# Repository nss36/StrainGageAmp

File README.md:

# StrainGageAmp
Nicholas Szczecinski 2020
West Virginia University
Morgantown, West Virginia, USA

EAGLE files for a 5V, 3-channel amplifier for 350 Ohm strain gages.

On Digikey:
Strain gauges -                    1033-1009-ND
3 LM324 Quad Op Amps -             296-1391-5-ND
9 352 Ohm 0603 SMD Resistors -     13-RT0603DRE07352RLCT-ND 
6 2.2 kOhm 0603 SMD Resistors -    P121436CT-ND
6 560 kOhm 0603 SMD Resistors -    749-1753-1-ND 

You will also need 11 pinheaders: one group of 5, and three groups of 2.

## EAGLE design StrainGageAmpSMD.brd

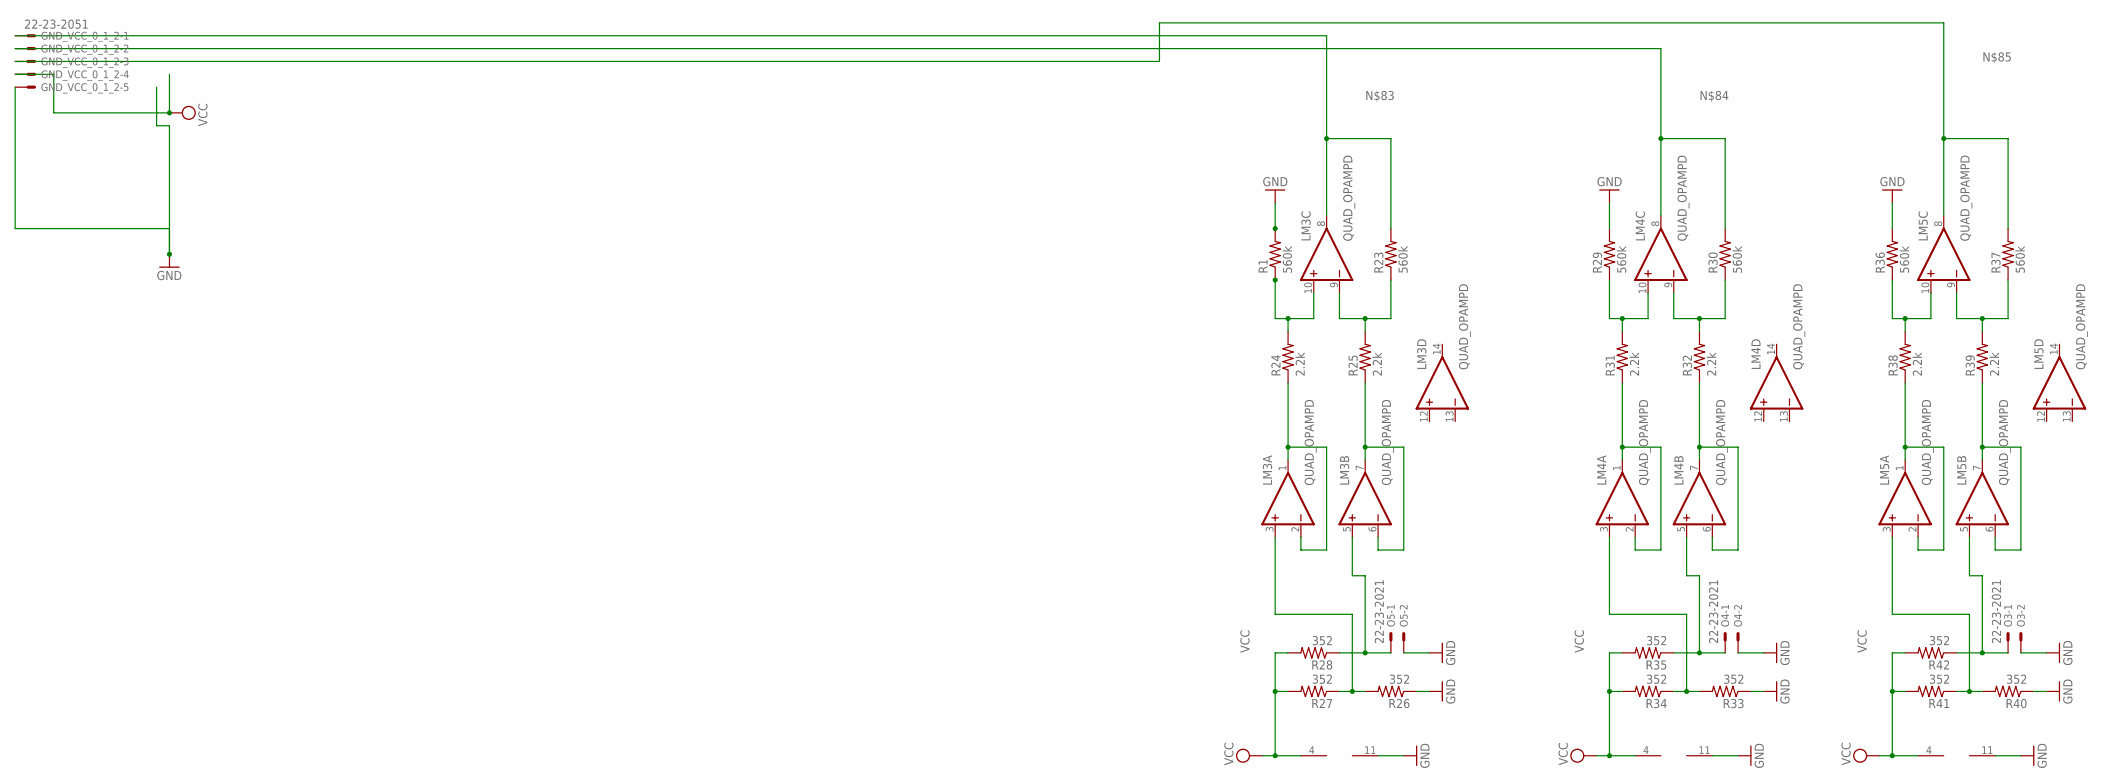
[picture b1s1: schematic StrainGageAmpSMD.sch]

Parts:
GND_VCC_0_1_2: 22-23-2051
LM3, LM4, LM5: QUAD_OPAMPD; SO14
O3, O4, O5: 22-23-2021
R1, R23, R29, R30, R36, R37: 560k; R0603
R24, R25, R31, R32, R38, R39: 2.2k; R0603
R26, R27, R28, R33, R34, R35, R40, R41, R42: 352; R0603

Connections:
GND: GND_VCC_0_1_2.5, LM3.11 (V-), LM4.11 (V-), LM5.11 (V-), O3.2, O4.2, O5.2, R1.2, R26.1, R29.2, R33.1, R36.2, R40.1
unnamed: LM3.3 (+IN), R26.2, R27.1
unnamed: LM3.5 (+IN), O5.1, R28.1
unnamed: LM3.1 (OUT), LM3.2 (-IN), R24.1
unnamed: LM3.6 (-IN), LM3.7 (OUT), R25.1
unnamed: LM3.9 (-IN), R23.1, R25.2
unnamed: LM3.10 (+IN), R1.1, R24.2
unnamed: LM4.3 (+IN), R33.2, R34.1
unnamed: LM4.5 (+IN), O4.1, R35.1
unnamed: LM4.1 (OUT), LM4.2 (-IN), R31.1
unnamed: LM4.6 (-IN), LM4.7 (OUT), R32.1
unnamed: LM4.9 (-IN), R30.1, R32.2
unnamed: LM4.10 (+IN), R29.1, R31.2
unnamed: LM5.3 (+IN), R40.2, R41.1
unnamed: LM5.5 (+IN), O3.1, R42.1
unnamed: LM5.1 (OUT), LM5.2 (-IN), R38.1
unnamed: LM5.6 (-IN), LM5.7 (OUT), R39.1
unnamed: LM5.9 (-IN), R37.1, R39.2
unnamed: LM5.10 (+IN), R36.1, R38.2
unnamed: GND_VCC_0_1_2.1, LM3.8 (OUT), R23.2
unnamed: GND_VCC_0_1_2.2, LM4.8 (OUT), R30.2
unnamed: GND_VCC_0_1_2.3, LM5.8 (OUT), R37.2
VCC: GND_VCC_0_1_2.4, LM3.4 (V+), LM4.4 (V+), LM5.4 (V+), R27.2, R28.2, R34.2, R35.2, R41.2, R42.2

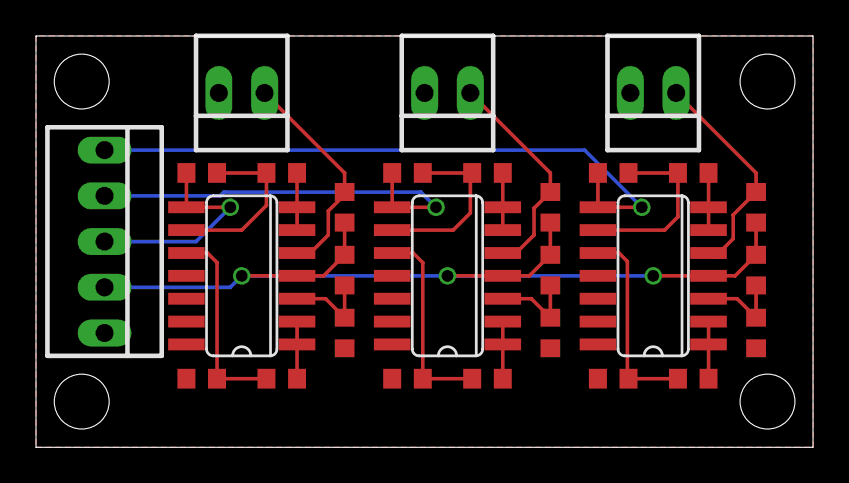
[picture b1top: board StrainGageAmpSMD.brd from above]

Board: 2 copper layers, 43.2 x 22.9 mm, 28 parts (0 on the bottom side), 23 nets.

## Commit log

2018-12-10 Initial upload of EAGLE design files
    Initial upload of EAGLE design files
2018-12-10 Updated file names
2018-12-10 Added CAM files
2020-12-11 Reduced from 6 channels to 3
    -Reduced 6 channels to 3
    -Changed all resistors to 0603 format
